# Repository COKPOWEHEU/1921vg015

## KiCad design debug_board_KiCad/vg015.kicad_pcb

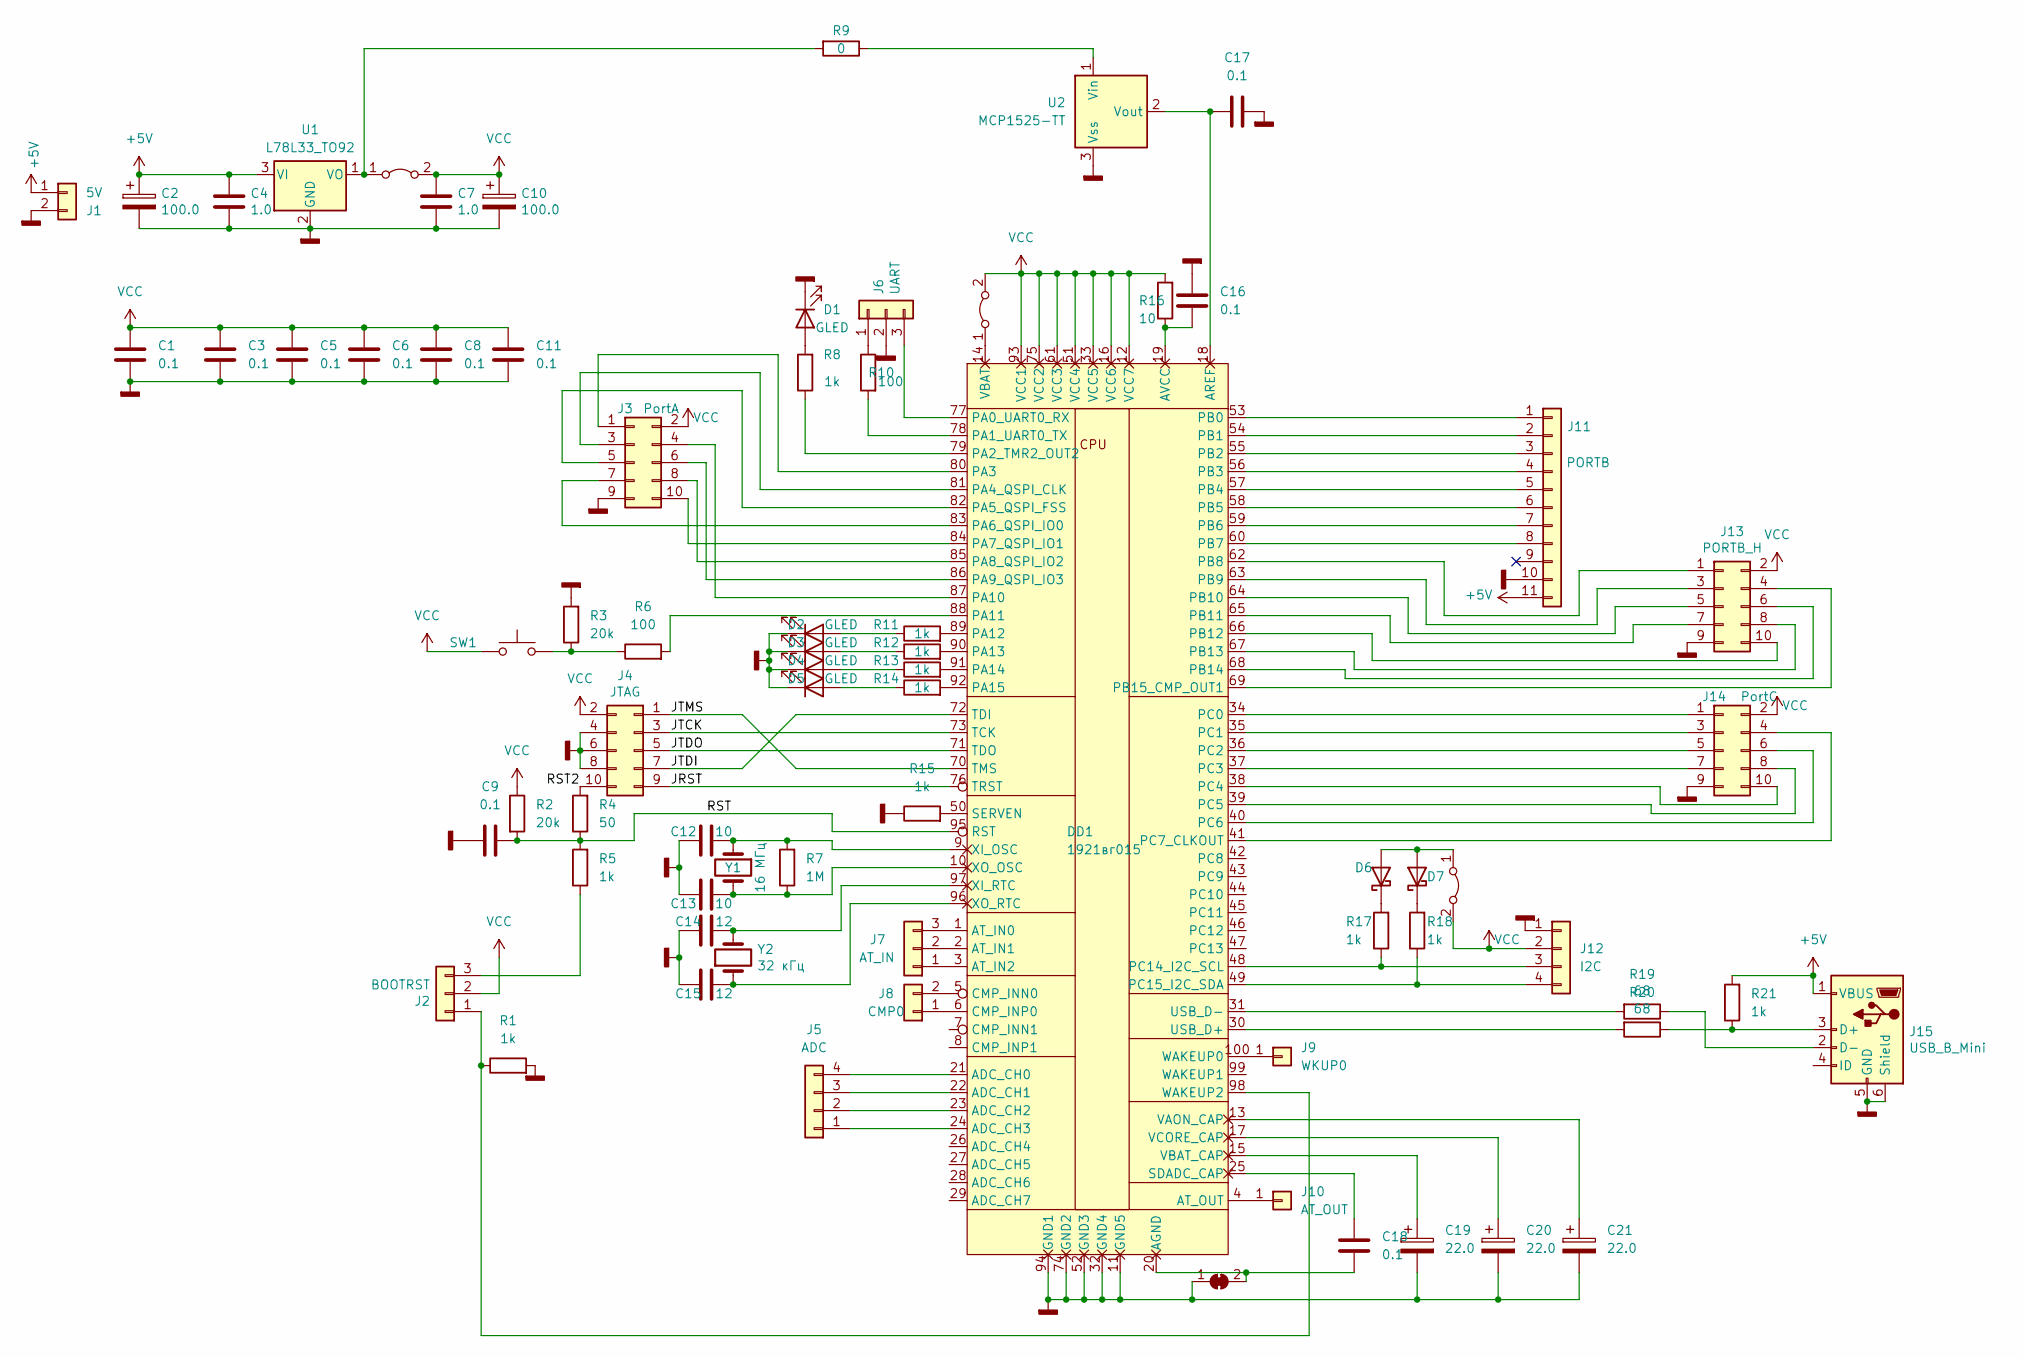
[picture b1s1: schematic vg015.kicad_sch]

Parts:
C1, C3, C5, C6, C8, C11: 0.1; C_0805_2012Metric
C2, C10: 100.0; CP_Radial_D6.3mm_P2.50mm
C4, C7: 1.0; C_Disc_D5.0mm_W2.5mm_P5.00mm
C9, C16, C17, C18: 0.1; C_Disc_D5.0mm_W2.5mm_P5.00mm
C12, C13: 10; C_Disc_D5.0mm_W2.5mm_P2.50mm
C14, C15: 12; C_Disc_D5.0mm_W2.5mm_P2.50mm
C19, C20, C21: 22.0; CP_Radial_D6.3mm_P2.50mm
D1, D2, D3, D4, D5: GLED; LED_D5.0mm_Clear
D6, D7: MBR0530; D_SOD-123
DD1: 1921вг015; LQFP-100_14x14mm_P0.5mm
J1: 5V; PinHeader_1x02_P2.54mm_Vertical
J2: BOOTRST; PinSocket_1x03_P2.54mm_Vertical
J3: PortA; IDC-Header_2x05_P2.54mm_Vertical
J4: JTAG; IDC-Header_2x05_P2.54mm_Vertical
J5: ADC; PinHeader_1x04_P2.54mm_Vertical
J6: UART; PinSocket_1x03_P2.54mm_Vertical
J7: AT_IN; PinSocket_1x03_P2.54mm_Vertical
J8: CMP0; PinHeader_1x02_P2.54mm_Vertical
J9: WKUP0; PinHeader_1x01_P2.54mm_Vertical
J10: AT_OUT; PinHeader_1x01_P2.54mm_Vertical
J11: PORTB; PinHeader_1x11_P2.54mm_Horizontal
J12: I2C; PinHeader_1x04_P2.54mm_Vertical
J13: PORTB_H; IDC-Header_2x05_P2.54mm_Vertical
J14: PortC; IDC-Header_2x05_P2.54mm_Vertical
J15: USB_B_Mini; USB-mini
JP1: PWR; PinHeader_1x02_P2.54mm_Vertical
JP2: VBAT; PinHeader_1x02_P2.54mm_Vertical
JP3: SolderJumper_2_Bridged; SolderJumper-2_P1.3mm_Bridged_Pad1.0x1.5mm
JP4: I2C_PWR; PinHeader_1x02_P2.54mm_Vertical
R1, R5, R8, R11, R12, R13, R14, R15, R17, R18, R21: 1k; R_0805_2012Metric
R2, R3: 20k; R_0805_2012Metric
R4: 50; R_0805_2012Metric
R6, R10: 100; R_0805_2012Metric
R7: 1M; R_0805_2012Metric
R9: 0; R_0805_2012Metric
R16: 10; R_0805_2012Metric
R19, R20: 68; R_0805_2012Metric
SW1: SW_PUSH_6mm_H8mm
U1: L78L33_TO92; TO-92_Inline_Wide
U2: MCP1525-TT; SOT-23-3
Y1: 16 МГц; Resonator-2Pin_W7.0mm_H2.5mm
Y2: 32 кГц; Crystal_AT310_D3.0mm_L10.0mm_Horizontal

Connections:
+5V: C2.1, C4.2, J1.1, J11.11, J15.1 (VBUS), R21.2, U1.3 (VI)
/JRST: DD1.76 (TRST), J4.9
/JTCK: DD1.73 (TCK), J4.3
/JTDI: DD1.72 (TDI), J4.7
/JTDO: DD1.71 (TDO), J4.5
/JTMS: DD1.70 (TMS), J4.1
/RST: C9.2, DD1.95 (RST), R2.2, R4.1, R5.2
/RST2: J4.10, R4.2
GNDD: C1.2, C2.2, C3.2, C4.1, C5.2, C6.2, C7.1, C8.2, C9.1, C10.2, C11.2, C12.1, C13.1, C14.2, C15.2, C16.1, C17.2, C19.2, C20.2, C21.2, D1.1 (K), D2.1 (K), D3.1 (K), D4.1 (K), D5.1 (K), DD1.11 (GND5), DD1.32 (GND4), DD1.52 (GND3), DD1.74 (GND2), DD1.94 (GND1), J1.2, J3.9, J4.4, J4.6, J4.8, J6.2, J11.10, J12.1, J13.9, J14.9, J15.5 (GND), J15.6 (Shield), JP3.1 (A), R1.2, R3.2, R15.1, U1.2 (GND), U2.3 (Vss)
unnamed: D1.2 (A), R8.2
unnamed: D2.2 (A), R11.1
unnamed: D3.2 (A), R12.1
unnamed: D4.2 (A), R13.1
unnamed: D5.2 (A), R14.1
unnamed: D6.2 (A), D7.2 (A), JP4.1 (A)
unnamed: D6.1 (K), R17.2
unnamed: D7.1 (K), R18.2
unnamed: DD1.21 (ADC_CH0), J5.4
unnamed: DD1.22 (ADC_CH1), J5.3
unnamed: DD1.23 (ADC_CH2), J5.2
unnamed: DD1.24 (ADC_CH3), J5.1
unnamed: C18.2, DD1.20 (AGND), JP3.2 (B)
unnamed: C17.1, DD1.18 (AREF), U2.2 (Vout)
unnamed: DD1.1 (AT_IN0), J7.3
unnamed: DD1.2 (AT_IN1), J7.2
unnamed: DD1.3 (AT_IN2), J7.1
unnamed: DD1.4 (AT_OUT), J10.1
unnamed: C16.2, DD1.19 (AVCC), R16.1
unnamed: DD1.5 (CMP_INN0), J8.2
unnamed: DD1.6 (CMP_INP0), J8.1
unnamed: DD1.77 (PA0_UART0_RX), J6.3
unnamed: DD1.78 (PA1_UART0_TX), R10.2
unnamed: DD1.79 (PA2_TMR2_OUT2), R8.1
unnamed: DD1.80 (PA3), J3.1
unnamed: DD1.81 (PA4_QSPI_CLK), J3.3
unnamed: DD1.82 (PA5_QSPI_FSS), J3.5
unnamed: DD1.83 (PA6_QSPI_IO0), J3.7
unnamed: DD1.84 (PA7_QSPI_IO1), J3.10
unnamed: DD1.85 (PA8_QSPI_IO2), J3.8
unnamed: DD1.86 (PA9_QSPI_IO3), J3.6
unnamed: DD1.87 (PA10), J3.4
unnamed: DD1.88 (PA11), R6.2
unnamed: DD1.89 (PA12), R11.2
unnamed: DD1.90 (PA13), R12.2
unnamed: DD1.91 (PA14), R13.2
unnamed: DD1.92 (PA15), R14.2
unnamed: DD1.53 (PB0), J11.1
unnamed: DD1.54 (PB1), J11.2
unnamed: DD1.55 (PB2), J11.3
unnamed: DD1.56 (PB3), J11.4
unnamed: DD1.57 (PB4), J11.5
unnamed: DD1.58 (PB5), J11.6
unnamed: DD1.59 (PB6), J11.7
unnamed: DD1.60 (PB7), J11.8
unnamed: DD1.62 (PB8), J13.1
unnamed: DD1.63 (PB9), J13.3
unnamed: DD1.64 (PB10), J13.5
unnamed: DD1.65 (PB11), J13.7
unnamed: DD1.66 (PB12), J13.10
unnamed: DD1.67 (PB13), J13.8
unnamed: DD1.68 (PB14), J13.6
unnamed: DD1.69 (PB15_CMP_OUT1), J13.4
unnamed: DD1.34 (PC0), J14.1
unnamed: DD1.35 (PC1), J14.3
unnamed: DD1.36 (PC2), J14.5
unnamed: DD1.37 (PC3), J14.7
unnamed: DD1.38 (PC4), J14.10
unnamed: DD1.39 (PC5), J14.8
unnamed: DD1.40 (PC6), J14.6
unnamed: DD1.41 (PC7_CLKOUT), J14.4
unnamed: DD1.48 (PC14_I2C_SCL), J12.3, R17.1
unnamed: DD1.49 (PC15_I2C_SDA), J12.4, R18.1
unnamed: C18.1, DD1.25 (SDADC_CAP)
unnamed: DD1.50 (SERVEN), R15.2
unnamed: DD1.30 (USB_D+), R20.2
unnamed: DD1.31 (USB_D-), R19.2
unnamed: C21.1, DD1.13 (VAON_CAP)
unnamed: DD1.14 (VBAT), JP2.1 (A)
unnamed: C19.1, DD1.15 (VBAT_CAP)
unnamed: C20.1, DD1.17 (VCORE_CAP)
unnamed: DD1.100 (WAKEUP0), J9.1
unnamed: DD1.98 (WAKEUP2), J2.1, R1.1
unnamed: C12.2, DD1.9 (XI_OSC), R7.2, Y1.1
unnamed: C14.1, DD1.97 (XI_RTC), Y2.2
unnamed: C13.2, DD1.10 (XO_OSC), R7.1, Y1.2
unnamed: C15.1, DD1.96 (XO_RTC), Y2.1
unnamed: J2.3, R5.1
unnamed: J6.1, R10.1
unnamed: J15.3 (D+), R20.1, R21.1
unnamed: J15.2 (D-), R19.1
unnamed: JP1.1 (A), R9.2, U1.1 (VO)
unnamed: R3.1, R6.1, SW1.2
unnamed: R9.1, U2.1 (Vin)
VCC: C1.1, C3.1, C5.1, C6.1, C7.2, C8.1, C10.1, C11.1, DD1.12 (VCC7), DD1.16 (VCC6), DD1.33 (VCC5), DD1.51 (VCC4), DD1.61 (VCC3), DD1.75 (VCC2), DD1.93 (VCC1), J2.2, J3.2, J4.2, J12.2, J13.2, J14.2, JP1.2 (B), JP2.2 (B), JP4.2 (B), R2.1, R16.2, SW1.1

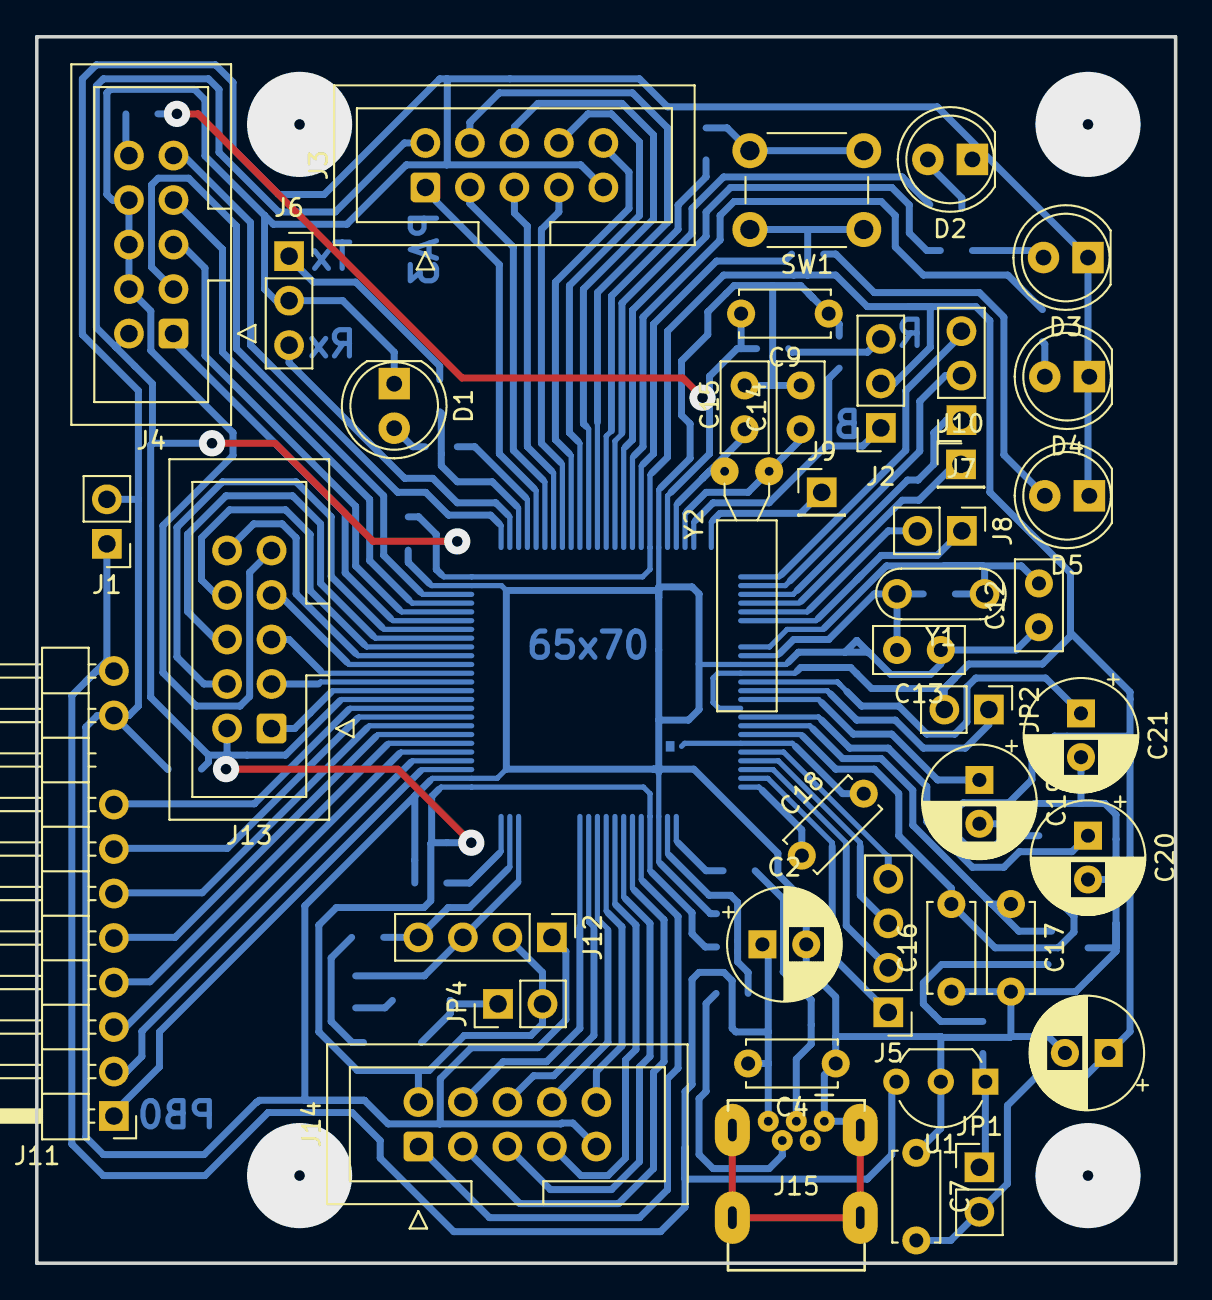
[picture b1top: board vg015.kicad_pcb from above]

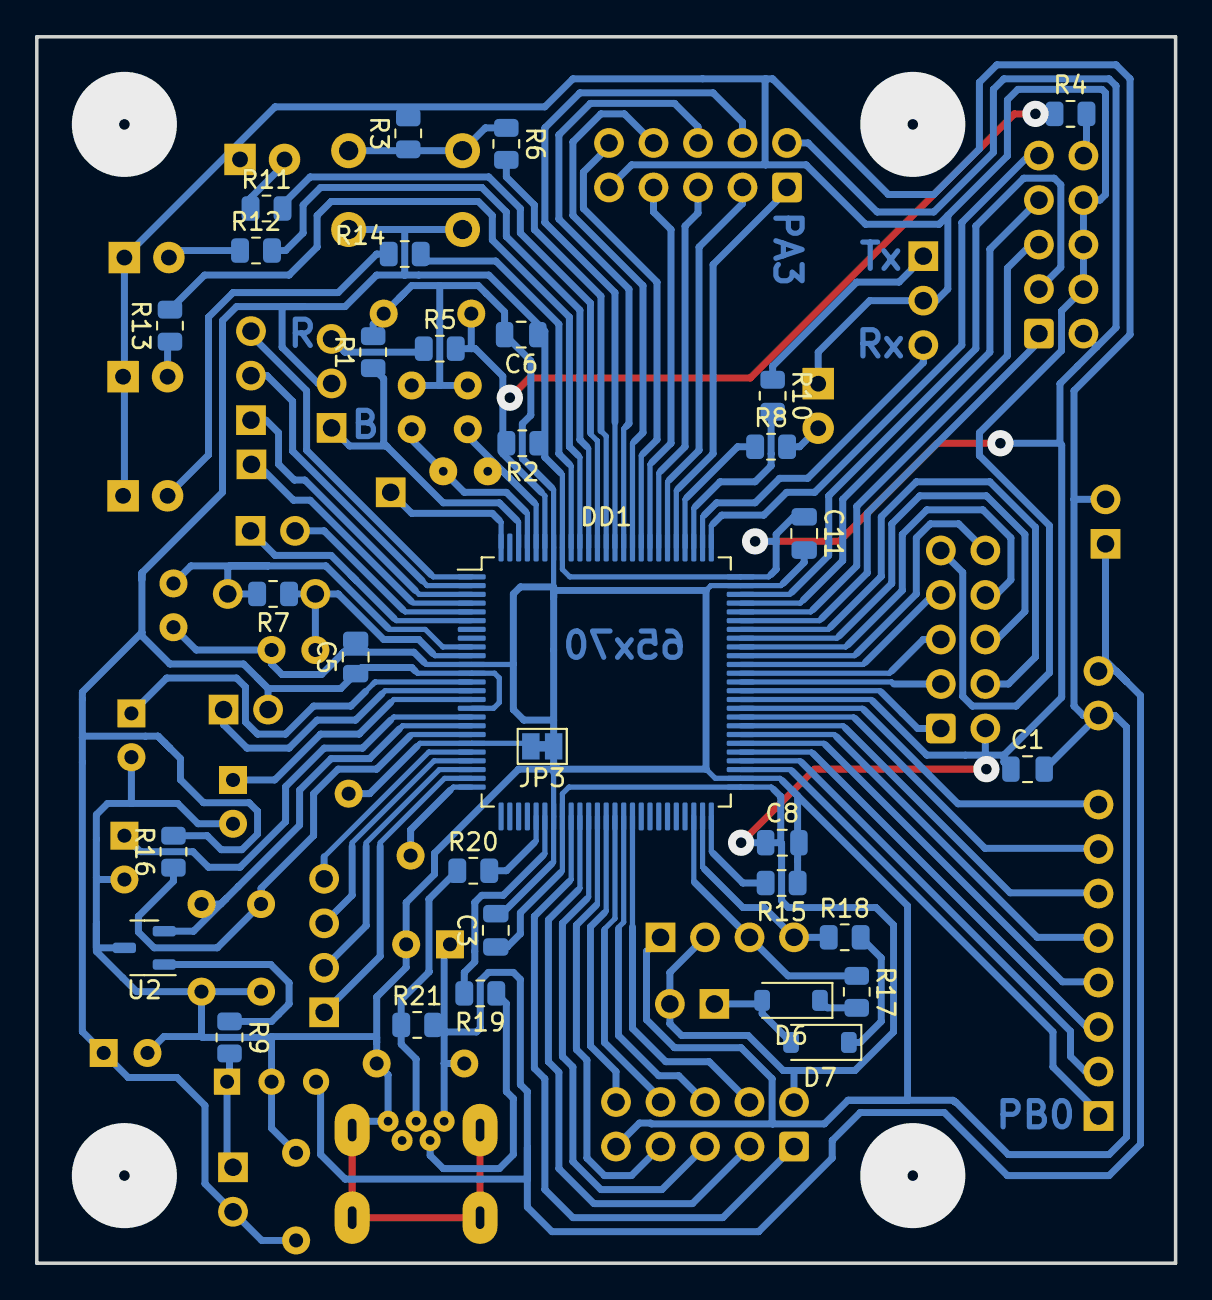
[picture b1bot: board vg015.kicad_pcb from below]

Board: 2 copper layers, 65.0 x 70.0 mm, 74 parts (32 on the bottom side), 94 nets.

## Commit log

2025-02-05 Initial commit: add manufacturer's library
2025-02-05 Add my 'startup' written in C
2025-02-05 Add datasheet
2025-02-05 Add test code
2025-02-05 Add debug board
2025-02-06 Add startup code written in C
2025-02-08 template project
2025-02-09 Add demo code for 3D graphics with ili9341
